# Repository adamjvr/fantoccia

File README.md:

# fantoccia
An Open Source DAQ hardare system based on https://github.com/marionette-daq/marionette-hardware

Quick Specs:
- STM32 ARM Cortex M7/M4 Dual Core MCU
- Lattice FPGA + open Tool Chain
- Automated Signal Muxing between MCU and FPGA
- USB C Interface
- Pheonix Contact Screw Terminal Interface + 2.54mm Headers
- Compatible with As man Open DAQ software systems as possible

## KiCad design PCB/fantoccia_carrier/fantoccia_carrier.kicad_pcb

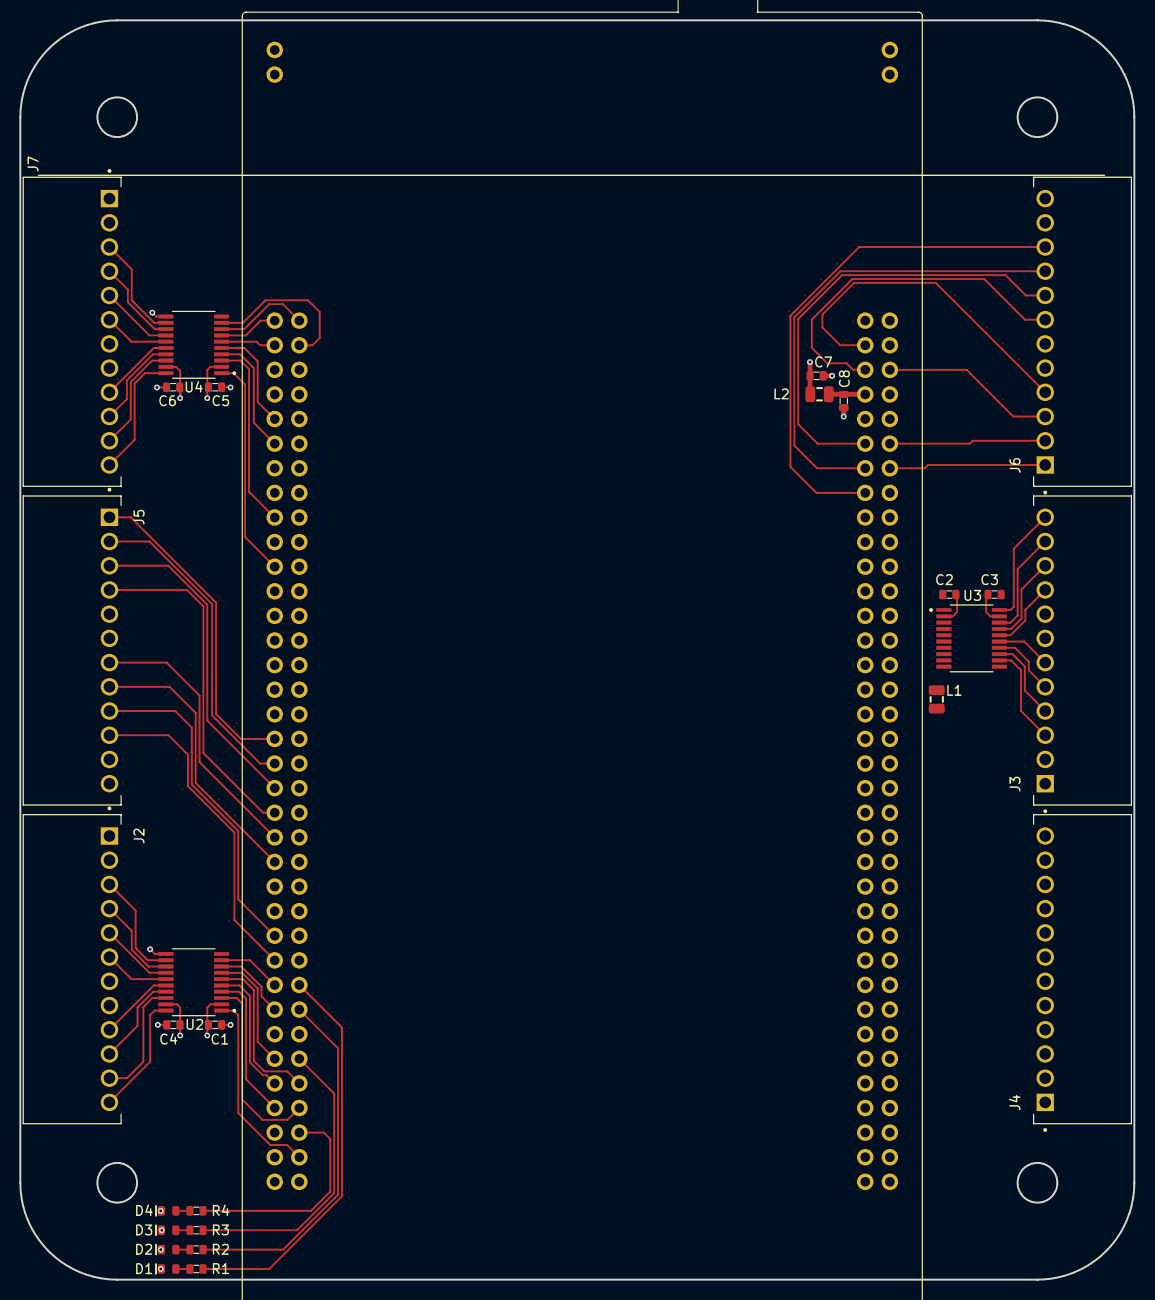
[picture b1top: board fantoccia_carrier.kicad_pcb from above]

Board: 4 copper layers, 115.0 x 130.0 mm, 29 parts (1 on the bottom side), 70 nets.

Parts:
C1, C2, C3, C4, C5, C6, C7, C8: CGA3E2X7R1H104K080AA; C0603
D1, D2, D3, D4: LTST-C194TBKT; LED0603
J1: BU2450SM-JJ-GTR
J2, J3, J4, J5, J6, J7: 1881545; PHOENIX_1881545
L1, L2: HZ0805E601R-10
R1, R2, R3, R4: RC0603FR-072K2L; R0603
U1: NUCLEO144-H743ZI; ST_Morpho_Connector_144_STLink
U2, U3, U4: TXS0108EPWR; SOP65P640X120-20N

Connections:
+3.3V: C1.1, C2.1, C5.1, C7.1, L2.1, U2.2 (VCCA), U3.2 (VCCA), U4.2 (VCCA)
+5V: C3.1, C4.1, C6.1, U2.19 (VCCB), U3.19 (VCCB), U4.19 (VCCB)
/Nucleo/3.3V_GPIO0: J5.1, U1.35 (PC2)
/Nucleo/3.3V_GPIO1: J5.2, U1.37 (PC3)
/Nucleo/3.3V_GPIO2: J5.3, U1.39 (PD4)
/Nucleo/3.3V_GPIO3: J5.4, U1.41 (PD5)
/Nucleo/3.3V_GPIO4: J5.7, U1.43 (PD6)
/Nucleo/3.3V_GPIO5: J5.8, U1.45 (PD7)
/Nucleo/3.3V_GPIO6: J5.9, U1.51 (PF1)
/Nucleo/3.3V_GPIO7: J5.10, U1.53 (PF0)
/Nucleo/3.3V_GPIO16: J6.1, U1.86 (USB_DM/PA11)
/Nucleo/3.3V_GPIO17: J6.2, U1.84 (USB_DP/PA12)
/Nucleo/3.3V_GPIO18: J6.3, U1.78 (ETH_RXD1/PC5)
/Nucleo/3.3V_GPIO19: J6.4, U1.75 (PB8)
/Nucleo/3.3V_GPIO20: J6.7, U1.77 (PB9)
/Nucleo/3.3V_GPIO21: J6.8, U1.83 (PA5)
/Nucleo/3.3V_GPIO22: J6.9, U1.85 (PA6)
/Nucleo/3.3V_GPIO23: J6.10, U1.87 (ETH_CRS_DV/PA7)
/Nucleo/CV_GPIO0: U1.70 (PG11/ETH_TX_EN), U2.1 (A1)
/Nucleo/CV_GPIO1: U1.66 (PG10), U2.3 (A2)
/Nucleo/CV_GPIO2: U1.65 (PG12), U2.4 (A3)
/Nucleo/CV_GPIO3: U1.63 (PG9), U2.5 (A4)
/Nucleo/CV_GPIO4: U1.64 (PG15), U2.6 (A5)
/Nucleo/CV_GPIO5: U1.61 (PE1), U2.7 (A6)
/Nucleo/CV_GPIO6: U1.57 (PD0), U2.8 (A7)
/Nucleo/CV_GPIO7: U1.55 (PD1), U2.9 (A8)
/Nucleo/CV_GPIO16: U1.21 (LD2/PB7), U4.1 (A1)
/Nucleo/CV_GPIO17: U1.17 (PA15), U4.3 (A2)
/Nucleo/CV_GPIO18: U1.11 (PF7), U4.4 (A3)
/Nucleo/CV_GPIO19: U1.9 (PF6), U4.5 (A4)
/Nucleo/CV_GPIO20: U1.3 (PC12), U4.6 (A5)
/Nucleo/CV_GPIO21: U1.1 (PC10), U4.7 (A6)
/Nucleo/CV_GPIO22: U1.2 (PC11), U4.8 (A7)
/Nucleo/CV_GPIO23: U1.4 (PD2), U4.9 (A8)
/Nucleo/LED0: R4.1, U1.68 (PG13/ETH_TXD0)
/Nucleo/LED1: R3.1, U1.62 (PE6)
/Nucleo/LED2: R1.1, U1.56 (PF9)
/Nucleo/LED3: R2.1, U1.58 (PG1)
/Translator 5V/5V_GPIO0: J2.12, U2.20 (B1)
/Translator 5V/5V_GPIO1: J2.11, U2.18 (B2)
/Translator 5V/5V_GPIO2: J2.10, U2.17 (B3)
/Translator 5V/5V_GPIO3: J2.9, U2.16 (B4)
/Translator 5V/5V_GPIO4: J2.6, U2.15 (B5)
/Translator 5V/5V_GPIO5: J2.5, U2.14 (B6)
/Translator 5V/5V_GPIO6: J2.4, U2.13 (B7)
/Translator 5V/5V_GPIO7: J2.3, U2.12 (B8)
/Translator 5V/5V_GPIO8: J3.12, U3.20 (B1)
/Translator 5V/5V_GPIO9: J3.11, U3.18 (B2)
/Translator 5V/5V_GPIO10: J3.10, U3.17 (B3)
/Translator 5V/5V_GPIO11: J3.9, U3.16 (B4)
/Translator 5V/5V_GPIO12: J3.6, U3.15 (B5)
/Translator 5V/5V_GPIO13: J3.5, U3.14 (B6)
/Translator 5V/5V_GPIO14: J3.4, U3.13 (B7)
/Translator 5V/5V_GPIO15: J3.3, U3.12 (B8)
/Translator 5V/5V_GPIO16: J7.12, U4.20 (B1)
/Translator 5V/5V_GPIO17: J7.11, U4.18 (B2)
/Translator 5V/5V_GPIO18: J7.10, U4.17 (B3)
/Translator 5V/5V_GPIO19: J7.9, U4.16 (B4)
/Translator 5V/5V_GPIO20: J7.6, U4.15 (B5)
/Translator 5V/5V_GPIO21: J7.5, U4.14 (B6)
/Translator 5V/5V_GPIO22: J7.4, U4.13 (B7)
/Translator 5V/5V_GPIO23: J7.3, U4.12 (B8)
GND: C1.2, C2.2, C3.2, C4.2, C5.2, C6.2, C7.2, C8.2, D1.2, D2.2, D3.2, D4.2, J1.2 (-), J2.1, J2.2, J2.7, J2.8, J3.1, J3.2, J3.7, J3.8, J4.5, J4.6, J4.11, J4.12, J5.5, J5.6, J5.11, J5.12, J6.5, J6.6, J6.11, J6.12, J7.1, J7.2, J7.7, J7.8, L1.2, U1.8 (GND), U1.19 (GND), U1.20 (GND), U1.22 (GND), U1.49 (GND), U1.60 (GND), U1.71 (GND), U1.72 (GND), U1.81 (GND), U1.92 (GND), U1.111 (GND), U1.126 (GND), U1.135 (GND), U1.143 (GND), U1.144 (GND), U2.11 (GND), U3.11 (GND), U4.11 (GND)
unnamed: D1.1, R1.2
unnamed: D2.1, R2.2
unnamed: D3.1, R3.2
unnamed: D4.1, R4.2
unnamed: J1.1 (+), U1.33 (VBAT)
unnamed: L1.1, U1.104 (AGND)
unnamed: C8.1, L2.2, U1.79 (AVDD)

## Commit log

2024-03-21 Update README.md
    Quick specs added to readme WIP
2024-03-21 Project Created + Schematic Started
    Created the project and started schematic capture for evaluation board carrier variant of the Fantoccia. This version will use ST evaluation board for M7/M4 dual core MCU for a quick development cycl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
2024-03-22 PCB Created
    Schematic mostly finished, just need to figure out pinning and add more TVS protection. Created PCB might need to tweak footprint.
2024-03-25 PCB progress and feature updates
    Added another bank of 5V channels. PCB layout figured out, board shape defined. 3D model added to STM32 evaluation kit. Now just need to determine pinout and add protection circuitry to pins.
2024-03-26 Design Rules
    Created Design rules, added more IO connections, need to figure out pinning next.
2024-04-02 PCB and Pinout
    Progress made with PCB wiring eval board pins to pheonix connectors. Pinout almost completely chosen but subject to revision !
